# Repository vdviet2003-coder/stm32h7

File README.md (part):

# STM32H7 Sensorless FOC Motor Control

Firmware điều khiển động cơ PMSM theo phương pháp **Field-Oriented Control (FOC) không cảm biến vị trí (sensorless)** chạy trên vi điều khiển **STM32H723ZGTx**, sử dụng Sliding Mode Observer (SMO) để ước lượng góc và tốc độ rotor.

---

## Mục lục

1. [Tổng quan hệ thống](#1-tổng-quan-hệ-thống)
2. [Phần cứng và thông số động cơ](#2-phần-cứng-và-thông-số-động-cơ)
3. [Cấu trúc thư mục](#3-cấu-trúc-thư-mục)
4. [Sơ đồ khối điều khiển](#4-sơ-đồ-khối-điều-khiển)
5. [Luồng thực thi chính](#5-luồng-thực-thi-chính)
6. [Các module và logic chi tiết](#6-các-module-và-logic-chi-tiết)
   - 6.1 [conf.h – Cấu hình toàn cục](#61-confh--cấu-hình-toàn-cục)
   - 6.2 [FOC Transform – Clarke & Park](#62-foc-transform--clarke--park)
   - 6.3 [SVPWM – Space Vector PWM](#63-svpwm--space-vector-pwm)
   - 6.4 [ADC Driver – Đo dòng điện](#64-adc-driver--đo-dòng-điện)
   - 6.5 [Sensor – Hall & Encoder](#65-sensor--hall--encoder)
   - 6.6 [SMO – Sliding Mode Observer](#66-smo--sliding-mode-observer)
   - 6.7 [PID Controller](#67-pid-controller)
   - 6.8 [PI Clamping Controller](#68-pi-clamping-controller)
   - 6.9 [Speed Ramp Profiles](#69-speed-ramp-profiles)
   - 6.10 [UART DMA Library](#610-uart-dma-library)
7. [Máy trạng thái điều khiển (state machine)](#7-máy-trạng-thái-điều-khiển-state-machine)
   - 7.1 [Trạng thái chính (state)](#71-trạng-thái-chính-state)
   - 7.2 [Trạng thái SMO sensorless (state_smo)](#72-trạng-thái-smo-sensorless-state_smo)
8. [Cấu hình Timer và Ngắt](#8-cấu-hình-timer-và-ngắt)
9. [Thông số bộ điều khiển PID](#9-thông-số-bộ-điều-khiển-pid)
10. [Cấu hình Clock hệ thống](#10-cấu-hình-clock-hệ-thống)
11. [Build và nạp firmware](#11-build-và-nạp-firmware)

---

## 1. Tổng quan hệ thống

Hệ thống thực hiện điều khiển FOC hoàn chỉnh gồm 3 vòng điều khiển lồng nhau:

```
Tốc độ đặt (RPM/rad·s⁻¹)
        │
        ▼
  [Vòng tốc độ - PID]
        │  iq_ref
        ▼
  [Vòng dòng iq - PID] ──► vq
  [Vòng dòng id - PID] ──► vd    (id_ref = 0, kiểm soát từ thông)
        │
        ▼
  [Inv. Park] ──► vα, vβ
        │
        ▼
    [SVPWM] ──► TIM1 (PWM 3 pha)
        │
        ▼
     Động cơ
        │
        ▼
  [ADC] ─── iu, iv, iw
  [SMO] ─── θe, ωe  (sensorless)
        │
  [Clarke + Park] ──► id, iq (phản hồi)
```

---

## 2. Phần cứng và thông số động cơ

| Tham số | Giá trị |
|---------|---------|
| Vi điều khiển | STM32H723ZGTx |
| Toolchain | Keil MDK-ARM |
| Điện áp DC bus (VDC) | 60 V |
| Số cặp cực | 4 |
| Điện trở stator (Rs) | 5.83 Ω |
| Điện cảm stator (Ls) | 12.23 mH |
| Từ thông nam châm vĩnh cửu (ψf) | 0.0756 Wb |
| Tần số PWM | 20 kHz |
| Tần số vòng FOC | 40 kHz |
| Cảm biến dòng | LA-25-NP (Hall effect) |
| Điện trở đo | 120 Ω |
| Tỉ số biến đổi | 1:1000 (3 mA/A) |

### Phân công GPIO Hall sensor

| Tín hiệu | GPIO | Pin |
|----------|------|-----|
| Hall U | GPIOD | PIN_12 |
| Hall V | GPIOD | PIN_13 |
| Hall W | GPIOD | PIN_14 |

---

## 3. Cấu trúc thư mục

```
no encoder/
└── GPIO/
    ├── Core/
    │   ├── Inc/           # Header STM32 HAL (adc.h, tim.h, gpio.h, ...)
    │   └── Src/
    │       ├── main.c     # Vòng lặp chính, FOC ISR, khởi tạo
    │       ├── adc.c      # Cấu hình ADC HAL (injected mode)
    │       ├── tim.c      # Cấu hình Timer HAL
    │       ├── gpio.c     # Cấu hình GPIO
    │       ├── dma.c      # Cấu hình DMA
    │       └── usart.c    # Cấu hình UART
    ├── MDK-ARM/           # Mã nguồn ứng dụng + project Keil
    │   ├── conf.h         # *** Toàn bộ thông số hệ thống ***
    │   ├── foc_transform.c/h   # Clarke, Park, Inv.Park transforms
    │   ├── svpwm.c/h           # SVPWM 6 sector + bù dead-time
    │   ├── adc_driver.c/h      # Đọc dòng từ LA-25-NP
    │   ├── sensor.c/h          # Hall sensor + Encoder ABZ
    │   ├── smo.c/h             # Sliding Mode Observer
    │   ├── pid.c/h             # PID Tustin + anti-windup
    │   ├── pi_control.c/h      # PI clamping
    │   ├── scurve_ramp.c/h     # S-curve tốc độ
    │   ├── multi_ramp.c/h      # Multi-segment ramp
    │   └── uart_dma_lib.c/h    # UART DMA gửi/nhận
    └── Drivers/
        ├── CMSIS/         # CMSIS core, DSP library
        └── STM32H7xx_HAL_Driver/  # HAL drivers
```

---

## 4. Sơ đồ khối điều khiển

```
                    ┌─────────────────────────────────────────────┐
                    │               FOC LOOP (40 kHz - TIM6)      │
                    │                                             │
speed_ref ──►[Ramp]──►[PID_speed]──► iq_ref                     │
                                        │                        │
              id_ref=0 ───────────────► [PID_id] ──► vd          │
                    iq_ref ──────────► [PID_iq] ──► vq           │
                                                     │           │
                                              [Inv.Park(θe)]     │
                                                     │           │
                                              [SVPWM] ──► TIM1   │
                                                                 │
    ADC ──► [Clarke] ──► iα,iβ ──► [Park(θe)] ──► id, iq        │
                  │                                              │
                  └──► [SMO] ──► θe, ωe (sensorless feedback)   │
                    └─────────────────────────────────────────────┘
```

---

## 5. Luồng thực thi chính

### `main()` – Khởi tạo một lần

```
1. MPU_Config()           – Cấu hình vùng bộ nhớ (DMA non-cacheable)
2. SystemClock_Config()   – PLL: HSE → 440 MHz SYSCLK
3. MX_*_Init()            – Khởi tạo tất cả ngoại vi HAL
4. SVPWM_Init()           – Cài đặt TIM1 center-aligned PWM
5. SVPWM_Start()          – Bật PWM 3 pha + complementary
6. ADC_Driver_Init()      – Khởi động ADC injected mode
7. ADC_Driver_CalibrateOffset() – Lấy 100,000 mẫu để tính offset
8. Hall_Sensor_Init()     – Đọc trạng thái Hall ban đầu
9. Encoder_Sensor_Init()  – Cấu hình TIM2 (encoder mode)
10. UART_DMA_Init()       – Bật UART1 DMA RX/TX
11. PID_Init(x3)          – Khởi tạo 3 vòng PID (Id, Iq, Speed)
12. SMO_Init()            – Khởi tạo Sliding Mode Observer
13. while(1) {}           – Vòng lặp trống (mọi xử lý qua ISR)
```

---

## 6. Các module và logic chi tiết

### 6.1 `conf.h` – Cấu hình toàn cục

File duy nhất chứa tất cả hằng số hệ thống. Thay đổi thông số ở đây sẽ tác động toàn bộ firmware.

```c
#define POLE_PAIRS          4.0f
#define MOTOR_PWM_FREQ      20000.0f   // Hz
#define MOTOR_SPEED_CALC_FREQ 40000.0f // Hz (vòng FOC)
#define MOTOR_RS            5.83f      // Ω
#define MOTOR_LS            0.01223f   // H
#define MOTOR_PSI_F         0.075595f  // Wb
#define VDC_BUS             60.0f      // V
```

---

### 6.2 FOC Transform – Clarke & Park

**File**: `foc_transform.c/h`

Thực hiện các phép biến đổi tọa độ cơ bản của FOC:

#### Clarke Transform (3 pha → αβ cố định)
$$i_\alpha = \frac{2}{3}i_u - \frac{1}{3}i_v - \frac{1}{3}i_w$$
$$i_\beta = \frac{1}{\sqrt{3}}(i_v - i_w)$$

#### Park Transform (αβ → dq quay theo rotor)
$$i_d = i_\alpha \cos\theta_e + i_\beta \sin\theta_e$$
$$i_q = -i_\alpha \sin\theta_e + i_\beta \cos\theta_e$$

#### Inverse Park (dq → αβ)
$$v_\alpha = v_d \cos\theta_e - v_q \sin\theta_e$$
$$v_\beta = v_d \sin\theta_e + v_q \cos\theta_e$$

> **Lưu ý**: Dùng biến đổi **amplitude-invariant** (không nhân 2/3), phù hợp với điều khiển dòng trực tiếp.

---

### 6.3 SVPWM – Space Vector PWM

**File**: `svpwm.c/h`

Thuật toán SVPWM 6 sector, center-aligned, với bù dead-time tự động.

#### Các bước tính toán:

1. **Xác định sector** – Dùng phương pháp dấu (Sign Method):
   ```
   U1 = Vβ
   U2 = (√3/2)·Vα - 0.5·Vβ
   U3 = -(√3/2)·Vα - 0.5·Vβ
   N = sign(U1) + 2·sign(U2) + 4·sign(U3)  → tra bảng sector_table[]
   ```

2. **Tính thời gian vector X, Y, Z** (chuẩn hóa):
   $$X = \frac{\sqrt{3} V_\beta}{V_{DC}}, \quad Y = \frac{1.5V_\alpha + 0.5\sqrt{3}V_\beta}{V_{DC}}, \quad Z = \frac{1.5V_\alpha - 0.5\sqrt{3}V_\beta}{V_{DC}}$$

3. **Gán Tx, Ty theo sector** và xử lý overmodulation (chuẩn hóa nếu Tx+Ty > 1)

4. **Tính duty cycle 3 pha**:
   $$T_a = 0.5 + \frac{V_\alpha}{V_{DC}}, \quad T_b = 0.5 + \frac{-0.5V_\alpha + \frac{\sqrt{3}}{2}V_\beta}{V_{DC}}$$

5. **Bù dead-time** (tự động theo chiều dòng điện):
   - Dead-time: 0.484 µs (= 133 chu kỳ / 275 MHz)
   - Điện áp diode: 0.8 V
   - Bù dương/âm tùy thuộc vào dấu dòng pha

6. **Ghi CCR** vào TIM1 (Center-aligned mode)

---

### 6.4 ADC Driver – Đo dòng điện

**File**: `adc_driver.c/h`

Đọc dòng điện từ 3 cảm biến **LA-25-NP** (Hall effect, ratio 1:1000) qua ADC injected mode đồng bộ với PWM.

#### Công thức chuyển đổi:
$$I_P = \frac{2 \cdot V_{ADC} + V_{offset}}{-R_m \cdot n} = \frac{2 \cdot V_{ADC} - 2.5}{-120 \times 0.003}$$

Trong đó:
- $V_{ADC}$: điện áp đọc từ ADC (0..3.3V)
- $V_{offset}$ = -2.5 V (điểm zero của cảm biến)
- $R_m$ = 120 Ω (điện trở đo)
- $n$ = 0.003 (tỉ số biến đổi = 3mA/A)

#### Hiệu chỉnh offset:
Khi khởi động, `ADC_Driver_CalibrateOffset()` lấy **100,000 mẫu** ở trạng thái không tải để xác định giá trị offset DC, bù vào các lần đọc sau.

---

### 6.5 Sensor – Hall & Encoder

**File**: `sensor.c/h`

#### Hall Sensor
- 3 bit Hall (U, V, W) → 6 bước (step 1..6)
- Mỗi bước tương ứng góc điện 60°
- `HallSensor_Update()` gọi trong `HAL_TIM_IC_CaptureCallback` (TIM4)
- `Sensor_Get_Electrical_Angle_Hall()` trả về góc điện (rad)

| Step | Góc điện |
|------|----------|
| 1    | 0°       |
| 2    | 60°      |
| 3    | 120°     |
| 4    | 180°     |
| 5    | 240°     |
| 6    | 300°     |

#### Encoder ABZ
- TIM2 (32-bit) ở chế độ encoder quadrature
- 2500 PPR × 4 = 10,000 counts/vòng cơ
- `EncoderSensor_Update()` gọi trong TIM3 ISR (1 kHz)
- Hỗ trợ 3 phương pháp tính tốc độ:
  - **M method**: đếm xung trong thời gian cố định (tốc độ cao)
  - **T method**: đo thời gian giữa xung (tốc độ thấp)
  - **M/T method**: kết hợp hai phương pháp
  - **AUTO**: tự động chọn theo tốc độ

#### Bù trễ góc (Angle Prediction)
Trong vòng FOC, góc điện được dự đoán trước để bù trễ tính toán và ADC:
$$\theta_{pred} = \theta_{enc} + \omega_e \cdot (T_s + t_{delay})$$
Trong đó $t_{delay}$ = 3.87 µs (trễ ADC + tính toán).

---

### 6.6 SMO – Sliding Mode Observer

**File**: `smo.c/h`

Observer phi tuyến để ước lượng góc và tốc độ rotor **không cần encoder vật lý**. Triển khai theo mô hình dòng điện stator trong hệ tọa độ tĩnh αβ, kết hợp bộ lọc thông thấp và PLL để trích xuất sức phản điện (back-EMF).

---

#### Nguyên lý tổng quát

```
  [u_α, u_β]           [i_α, i_β]
       │                    │
       ▼                    │
  ┌─────────────────┐       │
  │  Mô hình dòng   │◄──────┘   (sai lệch → z_α, z_β)
  │  điện stator    │
  │  (Euler)        │──► [î_α, î_β]
  └────────┬────────┘
           │ z_α, z_β (sliding output)
           ▼
     [LPF 500 Hz]──► [ê_α, ê_β]  (back-EMF ước lượng)
           │
           ▼
       [PLL 200 Hz]──► θ_est, ω_est
           │
           ▼
   [Bù pha LPF]──► θ_compensated
```

---

#### Bước 1 – Hàm trượt (Sliding function) với deadzone

Để giảm chattering (dao động cao tần tại mặt trượt), hàm sign được thay bằng hàm tuyến tính trong vùng deadzone:

```c
static inline float sign_function(float x, float deadzone) {
    if      (x >  deadzone) return  1.0f;
    else if (x < -deadzone) return -1.0f;
    else                    return  x / deadzone;  // tuyến tính trong [-dz, +dz]
}
```

Ngõ ra khuếch đại trượt:

$$
z_{\alpha} = K_s \cdot \text{sign}(i_{\alpha,est} - i_{\alpha},\ 0.1\,\text{A})
$$

$$
z_{\beta} = K_s \cdot \text{sign}(i_{\beta,est} - i_{\beta},\ 0.1\,\text{A})
$$

Hệ số trượt $K_s$ chọn đủ lớn để đảm bảo điều kiện trượt:
$$K_s = 1.5 \cdot \omega_{max,elec} \cdot \psi_f \quad [\text{V}]$$

Ví dụ: $\omega_{max}$ = 3000 RPM × 4 pp × 2π/60 ≈ 1257 rad/s → $K_s = 1.5 \times 1257 \times 0.0756 \approx 142\,\text{V}$

---

#### Bước 2 – Mô hình dòng điện stator (tích phân Euler)

$$\hat{i}_{\alpha}[k+1] = \hat{i}_{\alpha}[k] + \frac{T_s}{L_s}\left(u_\alpha - R_s \hat{i}_{\alpha}[k] - z_\alpha\right)$$
$$\hat{i}_{\beta}[k+1]  = \hat{i}_{\beta}[k]  + \frac{T_s}{L_s}\left(u_\beta  - R_s \hat{i}_{\beta}[k]  - z_\beta\right)$$

Khi đạt chế độ trượt ($s_\alpha \to 0$, $s_\beta \to 0$), $z_\alpha \approx e_\alpha$ và $z_\beta \approx e_\beta$ (sức phản điện thực).

---

#### Bước 3 – Lọc thông thấp trích xuất back-EMF

Bộ lọc IIR bậc 1 (forward Euler) với $f_c$ = 500 Hz:

$$
\hat{e}_{\alpha}[k] = \alpha_f \cdot z_{\alpha} + (1-\alpha_f) \cdot \hat{e}_{\alpha}[k-1]
$$

$$
\hat{e}_{\beta}[k] = \alpha_f \cdot z_{\beta} + (1-\alpha_f) \cdot \hat{e}_{\beta}[k-1]
$$

Hệ số lọc:
$$\alpha_f = \frac{\omega_c T_s}{1 + \omega_c T_s}, \quad \omega_c = 2\pi \times 500 \approx 3141.6\,\text{rad/s}$$

Tại $T_s = 25\,\mu\text{s}$: $\alpha_f \approx 0.0728$

> **Lưu ý**: Bộ lọc thông thấp gây trễ pha phụ thuộc tốc độ, được bù lại ở bước 5.

---

#### Bước 4 – PLL ước lượng góc và tốc độ

Tín hiệu lỗi PLL (cross-product):

$$
\varepsilon = \hat{e}_{\beta} \cos\hat{\theta} - \hat{e}_{\alpha} \sin\hat{\theta}
$$

Khi hội tụ: $\hat{\theta} \to \theta_{real}$ → $\varepsilon \to 0$.

Bộ điều khiển PI của PLL:
$$\hat{\omega} = K_{p,PLL} \cdot \varepsilon + K_{i,PLL} \cdot \int \varepsilon \, dt$$

Tích phân góc (Euler):
$$\hat{\theta}[k+1] = \hat{\theta}[k] + \hat{\omega} \cdot T_s$$

Chuẩn hóa về $[0, 2\pi)$ sau mỗi bước.

**Anti-windup tốc độ**: khi $|\hat{\omega}| > \omega_{max}$, giới hạn cứng và reset tích phân:
```c
if (omega_pll > smo->omega_max) {
    omega_pll = smo->omega_max;
    smo->pll_integral = omega_pll / smo->Ki_pll;   // back-calculation
}
```

**Thông số PLL** (thiết kế theo $\zeta = 1/\sqrt{2}$, $f_n$ = 200 Hz):

| Tham số | Công thức | Giá trị |
|---------|-----------|---------|
| $\omega_n$ | $2\pi \times 200$ | 1256.6 rad/s |
| $K_{p,PLL}$ | $\sqrt{2} \cdot \omega_n$ | ≈ 1777 |
| $K_{i,PLL}$ | $\omega_n^2$ | ≈ 1.58 × 10⁶ |

---

#### Bước 5 – Bù pha bộ lọc thông thấp (`SMO_GetCompensatedTheta`)

Bộ lọc thông thấp 500 Hz gây trễ pha phụ thuộc tốc độ. Góc thực được bù động:
$$\phi_{delay} = \arctan\!\left(\frac{\hat{\omega}}{\omega_c}\right)$$
$$\theta_{comp} = \hat{\theta} + \phi_{delay}$$

```c
float SMO_GetCompensatedTheta(SMO_Handle *smo) {
    float wc = 2.0f * M_PI * smo->fc_filter;
    float phase_delay = atan2f(smo->omega_est, wc);
    return smo->theta_est + phase_delay;
}
```

> Khác với xấp xỉ cố định $+\pi/2$, cách này bù chính xác ở mọi tốc độ: khi $\hat{\omega} \ll \omega_c$ thì $\phi \to 0$; khi $\hat{\omega} \gg \omega_c$ thì $\phi \to \pi/2$.

---

#### Tóm tắt cấu trúc `SMO_Handle`

| Trường | Ý nghĩa | Đơn vị |
|--------|---------|--------|
| `Rs`, `Ls`, `psi_f` | Thông số điện động cơ | Ω, H, Wb |
| `pole_pairs` | Số cặp cực | – |
| `Ks` | Hệ số khuếch đại trượt | V |
| `fc_filter`, `alpha_filter` | Bộ lọc LPF 500 Hz | Hz, – |
| `Kp_pll`, `Ki_pll` | Gains PI của PLL | – |
| `ialpha_est`, `ibeta_est` | Dòng ước lượng | A |
| `ealpha_est`, `ebeta_est` | Back-EMF ước lượng | V |
| `theta_est` | Góc điện ước lượng | rad |
| `omega_est` | Tốc độ điện ước lượng | rad/s |
| `pll_integral` | Tích phân PLL | – |
| `omega_max`, `omega_min` | Giới hạn tốc độ điện | rad/s |

---

#### API

| Hàm | Mô tả |
|-----|-------|
| `SMO_Init(...)` | Khởi tạo, tự tính Ks, α_filter, Kp/Ki_pll |
| `SMO_Update(smo, uα, uβ, iα, iβ, dt)` | Gọi mỗi chu kỳ FOC (40 kHz) |
| `SMO_GetCompensatedTheta(smo)` | Trả về góc đã bù trễ LPF (rad) |
| `SMO_GetOmega(smo)` | Trả về tốc độ điện (rad/s) |
| `SMO_GetSpeedRPM(smo)` | Trả về tốc độ cơ (RPM) |

---

### 6.7 PID Controller

**File**: `pid.c/h`

Bộ điều khiển PID rời rạc dùng **Tustin (bilinear) discretization** để bảo toàn tính ổn định.

#### Rời rạc hóa Tustin:
$$u[k] = u[k-1] + \alpha \cdot e[k] + \beta \cdot e[k-1] + \gamma \cdot e[k-2]$$

Trong đó:
$$\alpha = K_p + \frac{K_i T}{2} + \frac{2K_d}{T}, \quad \beta = K_i T - \frac{4K_d}{T}, \quad \gamma = -K_p + \frac{K_i T}{2} + \frac{2K_d}{T}$$

#### Anti-windup:
Khi ngõ ra bão hòa (|u| = u_max), bộ tích phân tạm dừng (conditional integration).

---

### 6.8 PI Clamping Controller

**File**: `pi_control.c/h`

Bộ PI đơn giản với clamping (giới hạn cứng ngõ ra):
$$I_{prev} = I_{prev} + K_i \cdot T_s \cdot e$$
$$u = \text{clamp}(K_p \cdot e + I_{prev}, U_{min}, U_{max})$$

Dùng làm bộ điều khiển dự phòng thay thế cho PID trong trường hợp cần tuning nhanh.

---

### 6.9 Speed Ramp Profiles

#### S-Curve Ramp (`scurve_ramp.c/h`)
Tạo profile tốc độ dạng chữ S để tránh thay đổi đột ngột:
- Tham số: gia tốc tăng, gia tốc giảm, hằng số thời gian lọc τ
- Lọc exponential qua linear ramp → output mượt mà

#### Multi-Segment Ramp (`multi_ramp.c/h`)
Gia tốc khác nhau ở các vùng tốc độ khác nhau:
- Dưới ngưỡng (`threshold`): dùng `AccUp_1`, `AccDown_1` (gia tốc thấp vùng thấp tốc)
- Trên ngưỡng: dùng `AccUp_2`, `AccDown_2` (gia tốc cao vùng cao tốc)

Cấu hình mặc định: `threshold=5`, `up1=10`, `up2=10`, `down1=20`, `down2=20` (rad/s²)

---

### 6.10 UART DMA Library

**File**: `uart_dma_lib.c/h`

Giao tiếp UART1 bằng DMA không chặn (non-blocking):
- **TX**: Gửi chuỗi/dữ liệu qua DMA, không chờ
- **RX**: Nhận bằng DMA + IDLE interrupt để phát hiện kết thúc frame
- Hỗ trợ callback: `UART_DMA_RegisterRxCallback()` để xử lý dữ liệu nhận

---

## 7. Máy trạng thái điều khiển (State Machine)

### 7.1 Trạng thái chính (`state`)

Biến `state` điều khiển chế độ hoạt động của vòng FOC (TIM6 ISR, 40kHz):

```
┌─────────────────────────────────────────────────────────────────────┐
│  state = 0  │  DỪNG – PWM output = 0, reset SMO, tắt LED          │
├─────────────────────────────────────────────────────────────────────┤
│  state = 1  │  ALIGN – Căn chỉnh rotor:                           │
│             │  · InvPark(Id=0.8A, Iq=0, θ=0) → vα, vβ            │
│             │  · Reset encoder sau khi căn                         │
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
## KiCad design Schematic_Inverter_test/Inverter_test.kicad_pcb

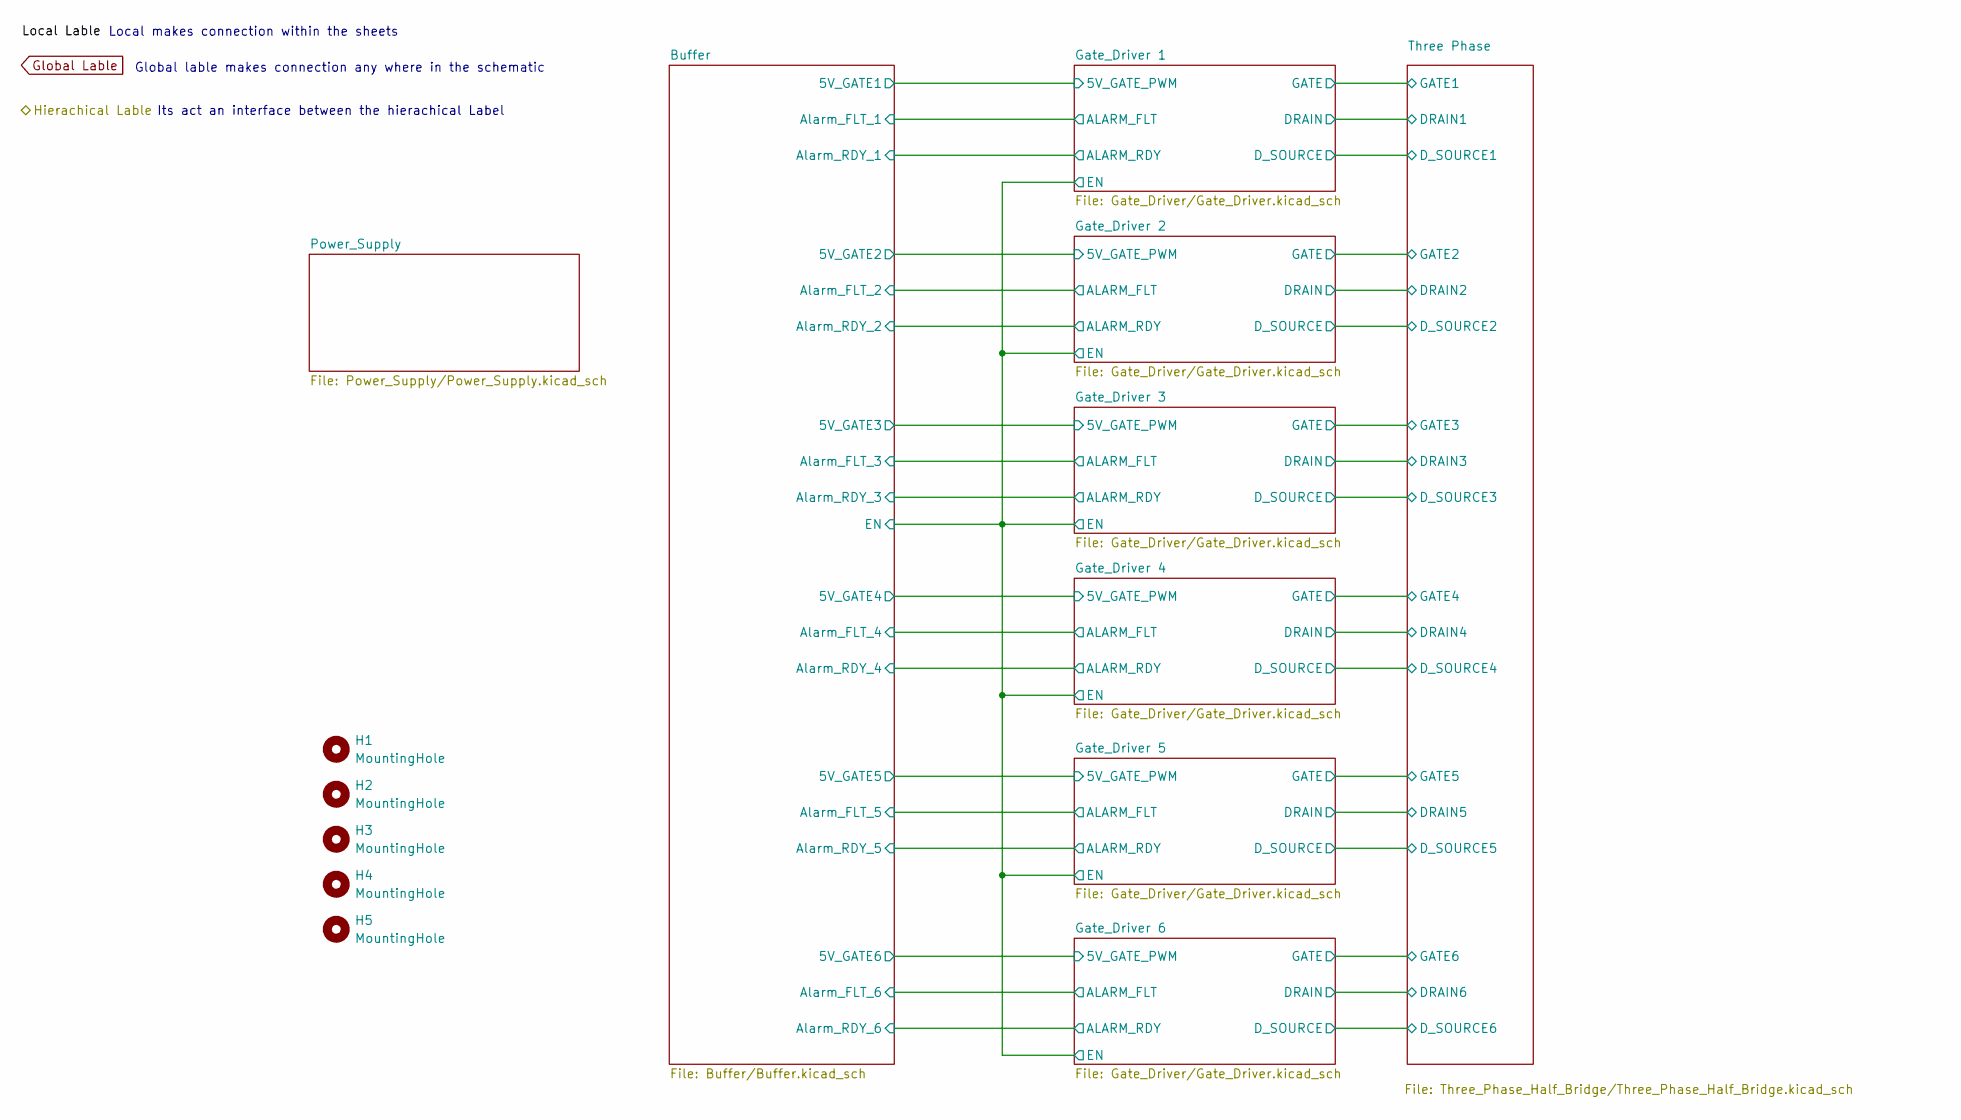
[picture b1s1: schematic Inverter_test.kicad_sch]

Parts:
H1, H2, H3, H4, H5: MountingHole; MountingHole_3.2mm_M3

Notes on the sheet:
Its act an interface between the hierachical Label
Global lable makes connection any where in the schematic
Local makes connection within the sheets

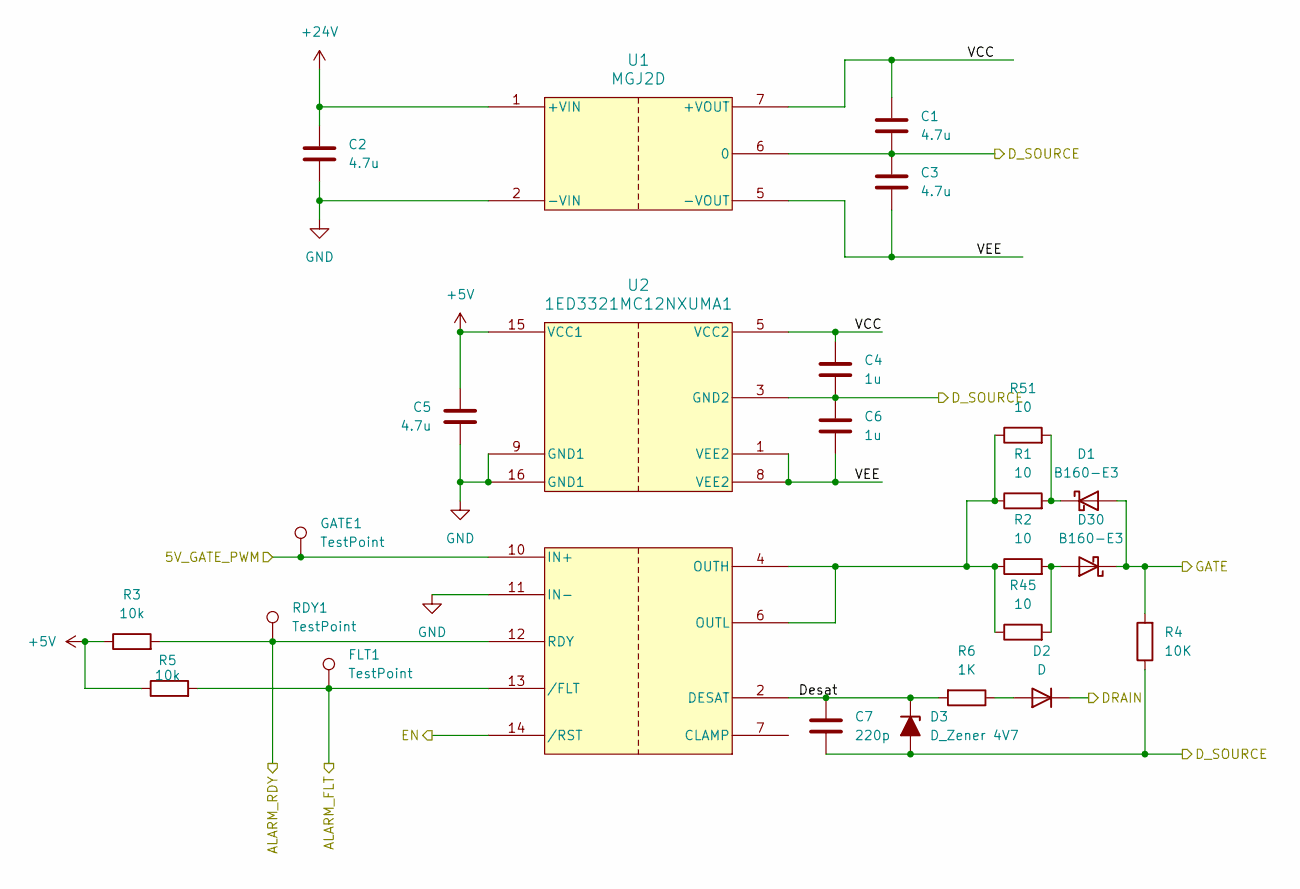
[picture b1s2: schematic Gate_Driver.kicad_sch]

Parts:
C1, C2, C3, C5: 4.7u; C_1206_3216Metric_Pad1.33x1.80mm_HandSolder
C4, C6: 1u; C_1206_3216Metric_Pad1.33x1.80mm_HandSolder
C7: 220p; C_1206_3216Metric_Pad1.33x1.80mm_HandSolder
D1, D30: B160-E3; D_SMA
D2: D; D_SMA
D3: D_Zener 4V7; D_SMA
FLT1: TestPoint; Pin_D0.7mm_L6.5mm_W1.8mm_FlatFork
GATE1: TestPoint; Pin_D0.7mm_L6.5mm_W1.8mm_FlatFork
R1, R2, R45, R51: 10; R_1206_3216Metric_Pad1.30x1.75mm_HandSolder
R3, R5: 10k; R_1206_3216Metric_Pad1.30x1.75mm_HandSolder
R4: 10K; R_1206_3216Metric_Pad1.30x1.75mm_HandSolder
R6: 1K; R_1206_3216Metric_Pad1.30x1.75mm_HandSolder
RDY1: TestPoint; Pin_D0.7mm_L6.5mm_W1.8mm_FlatFork
U1: MGJ2D; MGJ2_MUR
U2: 1ED3321MC12NXUMA1; PG-DSO-16-40_INF-M

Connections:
+5V: C5.1, R3.1, R5.1, U2.15 (VCC1); also elsewhere on the board
+24V: C2.1, U1.1 (+VIN); also elsewhere on the board
/Buffer/5V_DRIVER_EN: U2.14 (/RST); also elsewhere on the board
/Buffer/5V_GATE1: GATE1.1, U2.10 (IN+); also elsewhere on the board
/Buffer/Alarm_FLT_1: FLT1.1, R5.2, U2.13 (/FLT); also elsewhere on the board
/Buffer/Alarm_RDY_1: R3.2, RDY1.1, U2.12 (RDY); also elsewhere on the board
/Gate_Driver 1/D_SOURCE: C1.2, C3.2, C4.2, C6.1, C7.2, D3.2 (A), R4.1, U1.6 (0), U2.3 (GND2); also elsewhere on the board
/Gate_Driver 1/Desat: C7.1, D3.1 (K), R6.2, U2.2 (DESAT)
/Gate_Driver 1/GATE: D1.2 (A), D30.1 (K), R4.2; also elsewhere on the board
/Gate_Driver 1/VCC: C1.1, C4.1, U1.7 (+VOUT), U2.5 (VCC2)
/Gate_Driver 1/VEE: C3.1, C6.2, U1.5 (-VOUT), U2.1 (VEE2), U2.8 (VEE2)
/Three Phase/+270V: D2.1 (K); also elsewhere on the board
GND: C2.2, C5.2, U1.2 (-VIN), U2.9 (GND1), U2.11 (IN-), U2.16 (GND1); also elsewhere on the board
unnamed: D1.1 (K), R1.2, R51.2
unnamed: D2.2 (A), R6.1
unnamed: D30.2 (A), R2.2, R45.2
unnamed: R1.1, R2.1, R45.1, R51.1, U2.4 (OUTH), U2.6 (OUTL)

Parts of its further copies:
C8, C9, C10, C12, C15, C16, C17, C19, C22, C23, C24, C26, C29, C30, C31, C33, C36, C37, C38, C40: 4.7u; C_1206_3216Metric_Pad1.33x1.80mm_HandSolder
C11, C13, C18, C20, C25, C27, C32, C34, C39, C41: 1u; C_1206_3216Metric_Pad1.33x1.80mm_HandSolder
C14, C21, C28, C35, C42: 220p; C_1206_3216Metric_Pad1.33x1.80mm_HandSolder
D4, D7, D10, D13, D16, D31, D32, D33, D34, D35: B160-E3; D_SMA
D5, D8, D11, D14, D17: D; D_SMA
D6, D9, D12, D15, D18: D_Zener 4V7; D_SMA
FLT2, FLT3, FLT4, FLT5, FLT6: TestPoint; Pin_D0.7mm_L6.5mm_W1.8mm_FlatFork
GATE2, GATE3, GATE4, GATE5, GATE6: TestPoint; Pin_D0.7mm_L6.5mm_W1.8mm_FlatFork
R7, R8, R13, R14, R19, R20, R25, R26, R31, R32, R46, R47, R48, R49, R50, R52, R53, R54, R55, R56: 10; R_1206_3216Metric_Pad1.30x1.75mm_HandSolder
R9, R11, R15, R17, R21, R23, R27, R29, R33, R35: 10k; R_1206_3216Metric_Pad1.30x1.75mm_HandSolder
R10, R16, R22, R28, R34: 10K; R_1206_3216Metric_Pad1.30x1.75mm_HandSolder
R12, R18, R24, R30, R36: 1K; R_1206_3216Metric_Pad1.30x1.75mm_HandSolder
RDY2, RDY3, RDY4, RDY5, RDY6: TestPoint; Pin_D0.7mm_L6.5mm_W1.8mm_FlatFork
U3, U5, U7, U9, U11: MGJ2D; MGJ2_MUR
U4, U6, U8, U10, U12: 1ED3321MC12NXUMA1; PG-DSO-16-40_INF-M

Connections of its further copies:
+5V: C12.1, C19.1, C26.1, C33.1, C40.1, R9.1, R11.1, R15.1, R17.1, R21.1, R23.1, R27.1, R29.1, R33.1, R35.1, U4.15 (VCC1), U6.15 (VCC1), U8.15 (VCC1), U10.15 (VCC1), U12.15 (VCC1); also elsewhere on the board
+24V: C9.1, C16.1, C23.1, C30.1, C37.1, U3.1 (+VIN), U5.1 (+VIN), U7.1 (+VIN), U9.1 (+VIN), U11.1 (+VIN); also elsewhere on the board
/Buffer/5V_DRIVER_EN: U4.14 (/RST), U6.14 (/RST), U8.14 (/RST), U10.14 (/RST), U12.14 (/RST); also elsewhere on the board
/Buffer/5V_GATE2: GATE2.1, U4.10 (IN+); also elsewhere on the board
/Buffer/5V_GATE3: GATE3.1, U6.10 (IN+); also elsewhere on the board
/Buffer/5V_GATE4: GATE4.1, U8.10 (IN+); also elsewhere on the board
/Buffer/5V_GATE5: GATE5.1, U10.10 (IN+); also elsewhere on the board
/Buffer/5V_GATE6: GATE6.1, U12.10 (IN+); also elsewhere on the board
/Buffer/Alarm_FLT_2: FLT2.1, R11.2, U4.13 (/FLT); also elsewhere on the board
/Buffer/Alarm_FLT_3: FLT3.1, R17.2, U6.13 (/FLT); also elsewhere on the board
/Buffer/Alarm_FLT_4: FLT4.1, R23.2, U8.13 (/FLT); also elsewhere on the board
/Buffer/Alarm_FLT_5: FLT5.1, R29.2, U10.13 (/FLT); also elsewhere on the board
/Buffer/Alarm_FLT_6: FLT6.1, R35.2, U12.13 (/FLT); also elsewhere on the board
/Buffer/Alarm_RDY_2: R9.2, RDY2.1, U4.12 (RDY); also elsewhere on the board
/Buffer/Alarm_RDY_3: R15.2, RDY3.1, U6.12 (RDY); also elsewhere on the board
/Buffer/Alarm_RDY_4: R21.2, RDY4.1, U8.12 (RDY); also elsewhere on the board
/Buffer/Alarm_RDY_5: R27.2, RDY5.1, U10.12 (RDY); also elsewhere on the board
/Buffer/Alarm_RDY_6: R33.2, RDY6.1, U12.12 (RDY); also elsewhere on the board
/Gate_Driver 2/D_SOURCE: C8.2, C10.2, C11.2, C13.1, C14.2, D6.2 (A), R10.1, U3.6 (0), U4.3 (GND2); also elsewhere on the board
/Gate_Driver 2/Desat: C14.1, D6.1 (K), R12.2, U4.2 (DESAT)
/Gate_Driver 2/GATE: D4.2 (A), D31.1 (K), R10.2; also elsewhere on the board
/Gate_Driver 2/VCC: C8.1, C11.1, U3.7 (+VOUT), U4.5 (VCC2)
/Gate_Driver 2/VEE: C10.1, C13.2, U3.5 (-VOUT), U4.1 (VEE2), U4.8 (VEE2)
/Gate_Driver 3/D_SOURCE: C15.2, C17.2, C18.2, C20.1, C21.2, D9.2 (A), R16.1, U5.6 (0), U6.3 (GND2); also elsewhere on the board
/Gate_Driver 3/Desat: C21.1, D9.1 (K), R18.2, U6.2 (DESAT)
/Gate_Driver 3/GATE: D7.2 (A), D32.1 (K), R16.2; also elsewhere on the board
/Gate_Driver 3/VCC: C15.1, C18.1, U5.7 (+VOUT), U6.5 (VCC2)
/Gate_Driver 3/VEE: C17.1, C20.2, U5.5 (-VOUT), U6.1 (VEE2), U6.8 (VEE2)
/Gate_Driver 4/D_SOURCE: C22.2, C24.2, C25.2, C27.1, C28.2, D12.2 (A), R22.1, U7.6 (0), U8.3 (GND2); also elsewhere on the board
/Gate_Driver 4/Desat: C28.1, D12.1 (K), R24.2, U8.2 (DESAT)
/Gate_Driver 4/GATE: D10.2 (A), D33.1 (K), R22.2; also elsewhere on the board
/Gate_Driver 4/VCC: C22.1, C25.1, U7.7 (+VOUT), U8.5 (VCC2)
/Gate_Driver 4/VEE: C24.1, C27.2, U7.5 (-VOUT), U8.1 (VEE2), U8.8 (VEE2)
/Gate_Driver 5/D_SOURCE: C29.2, C31.2, C32.2, C34.1, C35.2, D15.2 (A), R28.1, U9.6 (0), U10.3 (GND2); also elsewhere on the board
/Gate_Driver 5/Desat: C35.1, D15.1 (K), R30.2, U10.2 (DESAT)
/Gate_Driver 5/GATE: D13.2 (A), D34.1 (K), R28.2; also elsewhere on the board
/Gate_Driver 5/VCC: C29.1, C32.1, U9.7 (+VOUT), U10.5 (VCC2)
/Gate_Driver 5/VEE: C31.1, C34.2, U9.5 (-VOUT), U10.1 (VEE2), U10.8 (VEE2)
/Gate_Driver 6/D_SOURCE: C36.2, C38.2, C39.2, C41.1, C42.2, D18.2 (A), R34.1, U11.6 (0), U12.3 (GND2); also elsewhere on the board
/Gate_Driver 6/Desat: C42.1, D18.1 (K), R36.2, U12.2 (DESAT)
/Gate_Driver 6/GATE: D16.2 (A), D35.1 (K), R34.2; also elsewhere on the board
/Gate_Driver 6/VCC: C36.1, C39.1, U11.7 (+VOUT), U12.5 (VCC2)
/Gate_Driver 6/VEE: C38.1, C41.2, U11.5 (-VOUT), U12.1 (VEE2), U12.8 (VEE2)
/Three Phase/+270V: D8.1 (K), D14.1 (K); also elsewhere on the board
/Three Phase/U: D5.1 (K); also elsewhere on the board
/Three Phase/V: D11.1 (K); also elsewhere on the board
/Three Phase/W: D17.1 (K); also elsewhere on the board
GND: C9.2, C12.2, C16.2, C19.2, C23.2, C26.2, C30.2, C33.2, C37.2, C40.2, U3.2 (-VIN), U4.9 (GND1), U4.11 (IN-), U4.16 (GND1), U5.2 (-VIN), U6.9 (GND1), U6.11 (IN-), U6.16 (GND1), U7.2 (-VIN), U8.9 (GND1), U8.11 (IN-), U8.16 (GND1), U9.2 (-VIN), U10.9 (GND1), U10.11 (IN-), U10.16 (GND1), U11.2 (-VIN), U12.9 (GND1), U12.11 (IN-), U12.16 (GND1); also elsewhere on the board
unnamed: D4.1 (K), R7.2, R52.2
unnamed: D5.2 (A), R12.1
unnamed: D7.1 (K), R13.2, R53.2
unnamed: D8.2 (A), R18.1
unnamed: D10.1 (K), R19.2, R54.2
unnamed: D11.2 (A), R24.1
unnamed: D13.1 (K), R25.2, R55.2
unnamed: D14.2 (A), R30.1
unnamed: D16.1 (K), R31.2, R56.2
unnamed: D17.2 (A), R36.1
unnamed: D31.2 (A), R8.2, R46.2
unnamed: D32.2 (A), R14.2, R47.2
unnamed: D33.2 (A), R20.2, R48.2
unnamed: D34.2 (A), R26.2, R49.2
unnamed: D35.2 (A), R32.2, R50.2
unnamed: R7.1, R8.1, R46.1, R52.1, U4.4 (OUTH), U4.6 (OUTL)
unnamed: R13.1, R14.1, R47.1, R53.1, U6.4 (OUTH), U6.6 (OUTL)
unnamed: R19.1, R20.1, R48.1, R54.1, U8.4 (OUTH), U8.6 (OUTL)
unnamed: R25.1, R26.1, R49.1, R55.1, U10.4 (OUTH), U10.6 (OUTL)
unnamed: R31.1, R32.1, R50.1, R56.1, U12.4 (OUTH), U12.6 (OUTL)

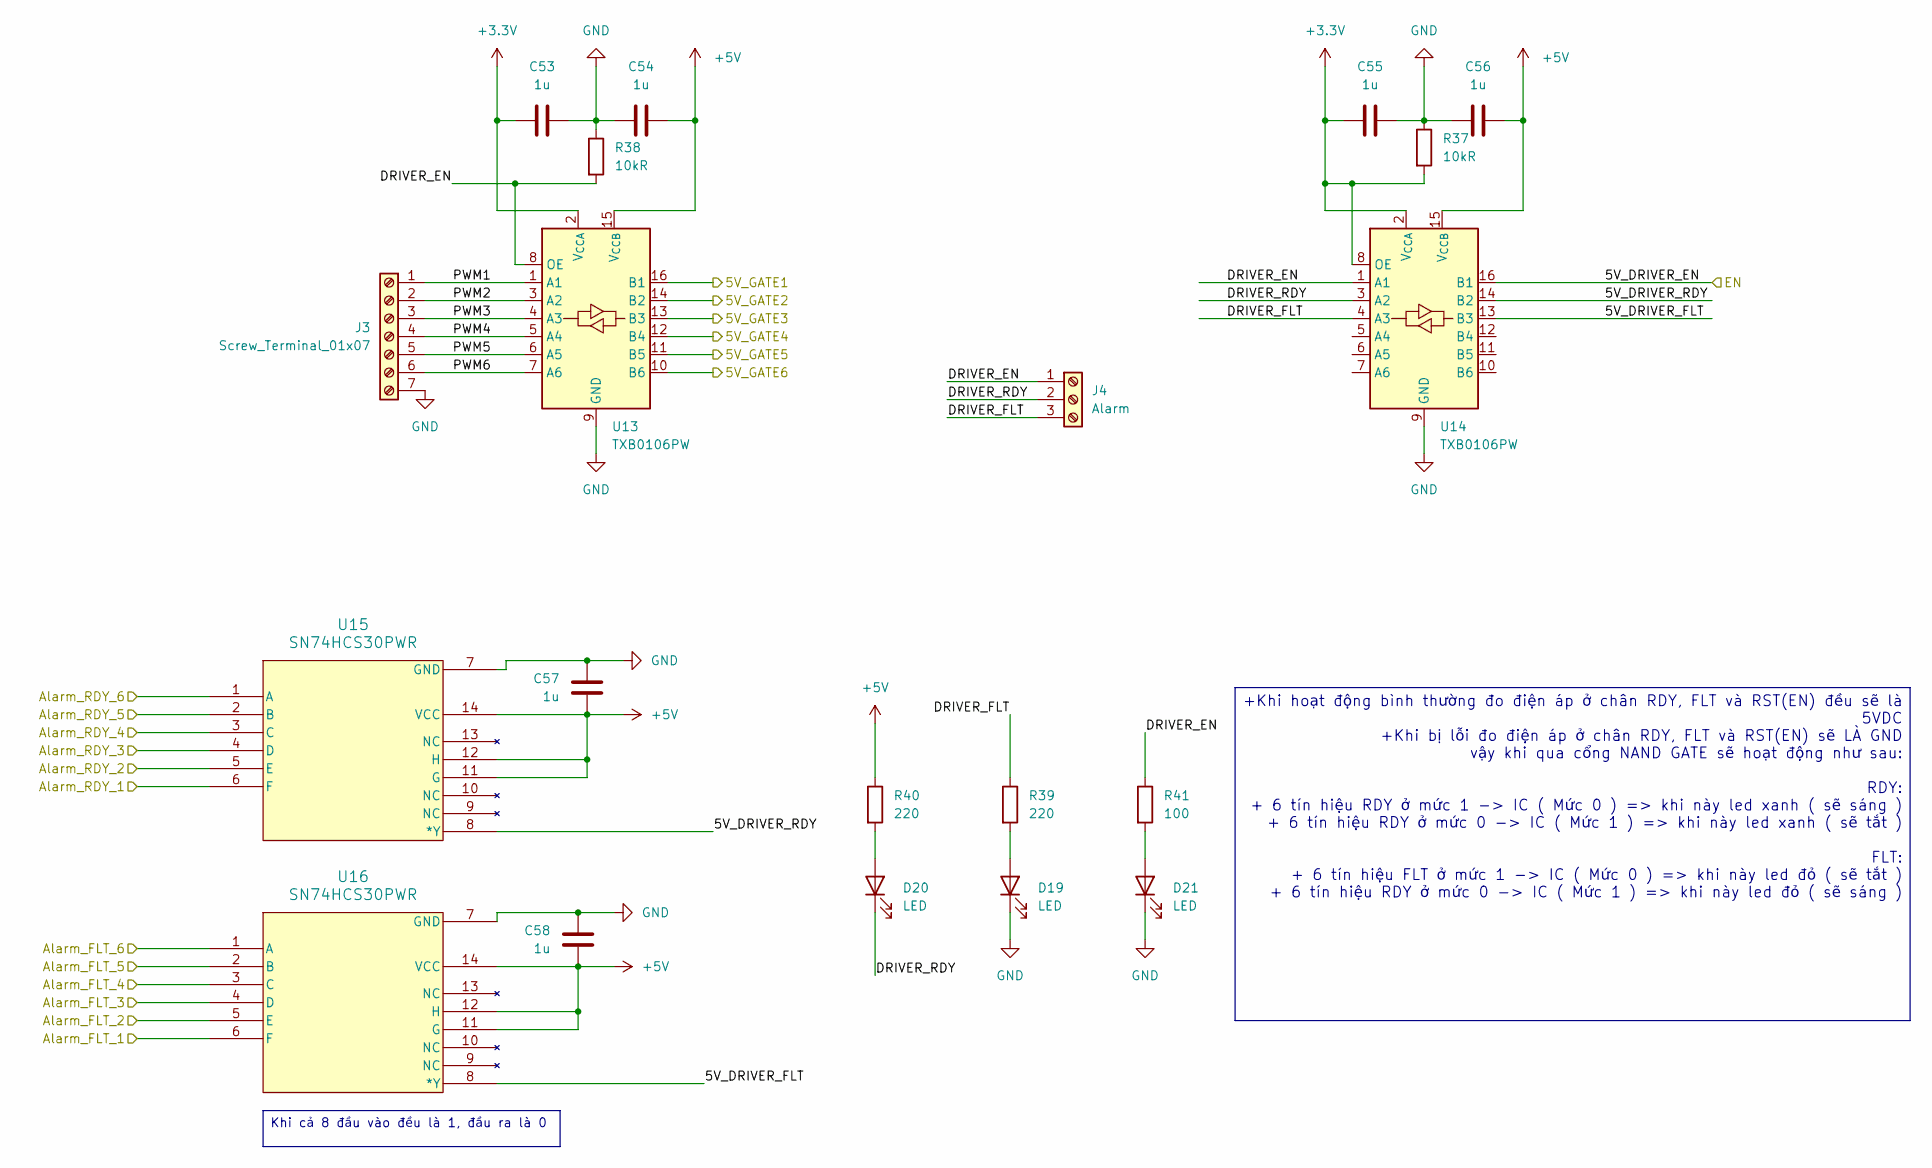
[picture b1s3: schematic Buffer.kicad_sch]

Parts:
C53, C54, C55, C56, C57, C58: 1u; C_1206_3216Metric_Pad1.33x1.80mm_HandSolder
D19, D20, D21: LED; LED_D3.0mm
J3: Screw_Terminal_01x07; TerminalBlock_Phoenix_MKDS-1,5-7_1x07_P5.00mm_Horizontal
J4: Alarm; TerminalBlock_Phoenix_MKDS-1,5-3_1x03_P5.00mm_Horizontal
R37, R38: 10kR; R_1206_3216Metric_Pad1.30x1.75mm_HandSolder
R39, R40: 220; R_1206_3216Metric_Pad1.30x1.75mm_HandSolder
R41: 100; R_1206_3216Metric_Pad1.30x1.75mm_HandSolder
U13, U14: TXB0106PW; TSSOP-16_4.4x5mm_P0.65mm
U15, U16: SN74HCS30PWR; SOIC-14_SN74HCS30PWR-M

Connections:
+3.3V: C53.2, C55.2, R37.2, U13.2 (V_{CCA}), U14.2 (V_{CCA}), U14.8 (OE); also elsewhere on the board
+5V: C54.1, C56.1, C57.2, C58.2, R40.1, U13.15 (V_{CCB}), U14.15 (V_{CCB}), U15.11 (G), U15.12 (H), U15.14 (VCC), U16.11 (G), U16.12 (H), U16.14 (VCC); also elsewhere on the board
/Buffer/5V_DRIVER_EN: U14.16 (B1); also elsewhere on the board
/Buffer/5V_DRIVER_FLT: U14.13 (B3), U16.8 (*Y)
/Buffer/5V_DRIVER_RDY: U14.14 (B2), U15.8 (*Y)
/Buffer/5V_GATE1: U13.16 (B1); also elsewhere on the board
/Buffer/5V_GATE2: U13.14 (B2); also elsewhere on the board
/Buffer/5V_GATE3: U13.13 (B3); also elsewhere on the board
/Buffer/5V_GATE4: U13.12 (B4); also elsewhere on the board
/Buffer/5V_GATE5: U13.11 (B5); also elsewhere on the board
/Buffer/5V_GATE6: U13.10 (B6); also elsewhere on the board
/Buffer/Alarm_FLT_1: U16.6 (F); also elsewhere on the board
/Buffer/Alarm_FLT_2: U16.5 (E); also elsewhere on the board
/Buffer/Alarm_FLT_3: U16.4 (D); also elsewhere on the board
/Buffer/Alarm_FLT_4: U16.3 (C); also elsewhere on the board
/Buffer/Alarm_FLT_5: U16.2 (B); also elsewhere on the board
/Buffer/Alarm_FLT_6: U16.1 (A); also elsewhere on the board
/Buffer/Alarm_RDY_1: U15.6 (F); also elsewhere on the board
/Buffer/Alarm_RDY_2: U15.5 (E); also elsewhere on the board
/Buffer/Alarm_RDY_3: U15.4 (D); also elsewhere on the board
/Buffer/Alarm_RDY_4: U15.3 (C); also elsewhere on the board
/Buffer/Alarm_RDY_5: U15.2 (B); also elsewhere on the board
/Buffer/Alarm_RDY_6: U15.1 (A); also elsewhere on the board
/Buffer/DRIVER_EN: J4.1, R38.2, R41.1, U13.8 (OE), U14.1 (A1)
/Buffer/DRIVER_FLT: J4.3, R39.1, U14.4 (A3)
/Buffer/DRIVER_RDY: D20.1 (K), J4.2, U14.3 (A2)
/Buffer/PWM1: J3.1, U13.1 (A1)
/Buffer/PWM2: J3.2, U13.3 (A2)
/Buffer/PWM3: J3.3, U13.4 (A3)
/Buffer/PWM4: J3.4, U13.5 (A4)
/Buffer/PWM5: J3.5, U13.6 (A5)
/Buffer/PWM6: J3.6, U13.7 (A6)
GND: C53.1, C54.2, C55.1, C56.2, C57.1, C58.1, D19.1 (K), D21.1 (K), J3.7, R37.1, R38.1, U13.9 (GND), U14.9 (GND), U15.7 (GND), U16.7 (GND); also elsewhere on the board
unnamed: D19.2 (A), R39.2
unnamed: D20.2 (A), R40.2
unnamed: D21.2 (A), R41.2

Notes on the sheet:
+Khi hoạt động bình thường đo điện áp ở chân RDY, FLT và RST(EN) đều sẽ là 5VDC +Khi bị lỗi đo điện áp ở chân RDY, FLT và RST(EN) sẽ LÀ GND vậy khi qua cổng NAND GATE sẽ hoạt động như sau: RDY: + 6 tín hiệu RDY ở mức 1 -> IC ( Mức 0 ) => khi này led xanh ( sẽ sáng ) + 6 tín hiệu RDY ở mức 0 -> IC (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
Khi cả 8 đầu vào đều là 1, đầu ra là 0

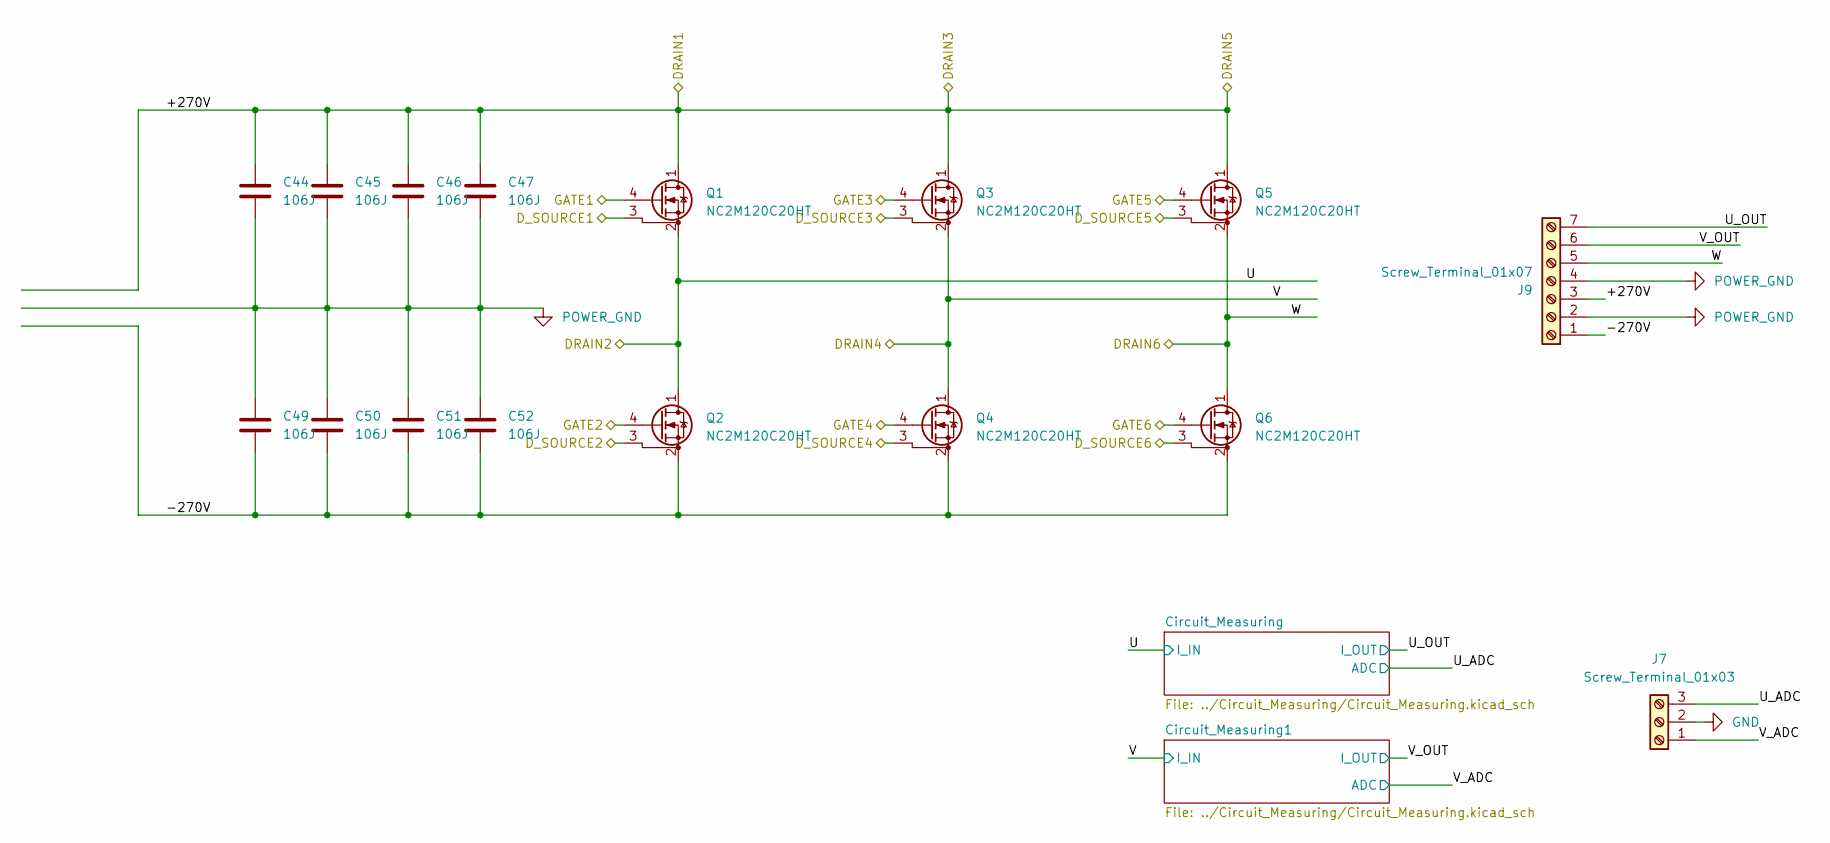
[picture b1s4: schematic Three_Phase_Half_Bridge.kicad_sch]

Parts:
C44, C45, C46, C47, C49, C50, C51, C52: 106J; C_Rect_L31.5mm_W15.0mm_P27.50mm_MKS4
J7: Screw_Terminal_01x03; TerminalBlock_Phoenix_MKDS-1,5-3_1x03_P5.00mm_Horizontal
J9: Screw_Terminal_01x07; Untitled
Q1, Q2, Q3, Q4, Q5, Q6: NC2M120C20HT; TO-247-4_Horizontal_TabUp

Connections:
/Gate_Driver 1/D_SOURCE: Q1.3 (DS); also elsewhere on the board
/Gate_Driver 1/GATE: Q1.4 (G); also elsewhere on the board
/Gate_Driver 2/D_SOURCE: Q2.3 (DS); also elsewhere on the board
/Gate_Driver 2/GATE: Q2.4 (G); also elsewhere on the board
/Gate_Driver 3/D_SOURCE: Q3.3 (DS); also elsewhere on the board
/Gate_Driver 3/GATE: Q3.4 (G); also elsewhere on the board
/Gate_Driver 4/D_SOURCE: Q4.3 (DS); also elsewhere on the board
/Gate_Driver 4/GATE: Q4.4 (G); also elsewhere on the board
/Gate_Driver 5/D_SOURCE: Q5.3 (DS); also elsewhere on the board
/Gate_Driver 5/GATE: Q5.4 (G); also elsewhere on the board
/Gate_Driver 6/D_SOURCE: Q6.3 (DS); also elsewhere on the board
/Gate_Driver 6/GATE: Q6.4 (G); also elsewhere on the board
/Three Phase/+270V: C44.1, C45.1, C46.1, C47.1, J9.3, Q1.1 (D), Q3.1 (D), Q5.1 (D); also elsewhere on the board
/Three Phase/-270V: C49.2, C50.2, C51.2, C52.2, J9.1, Q2.2 (S), Q4.2 (S), Q6.2 (S)
/Three Phase/U: Q1.2 (S), Q2.1 (D); also elsewhere on the board
/Three Phase/U_ADC: J7.3; also elsewhere on the board
/Three Phase/U_OUT: J9.7; also elsewhere on the board
/Three Phase/V: Q3.2 (S), Q4.1 (D); also elsewhere on the board
/Three Phase/V_ADC: J7.1; also elsewhere on the board
/Three Phase/V_OUT: J9.6; also elsewhere on the board
/Three Phase/W: J9.5, Q5.2 (S), Q6.1 (D); also elsewhere on the board
GND: J7.2; also elsewhere on the board
POWER_GND: C44.2, C45.2, C46.2, C47.2, C49.1, C50.1, C51.1, C52.1, J9.2, J9.4

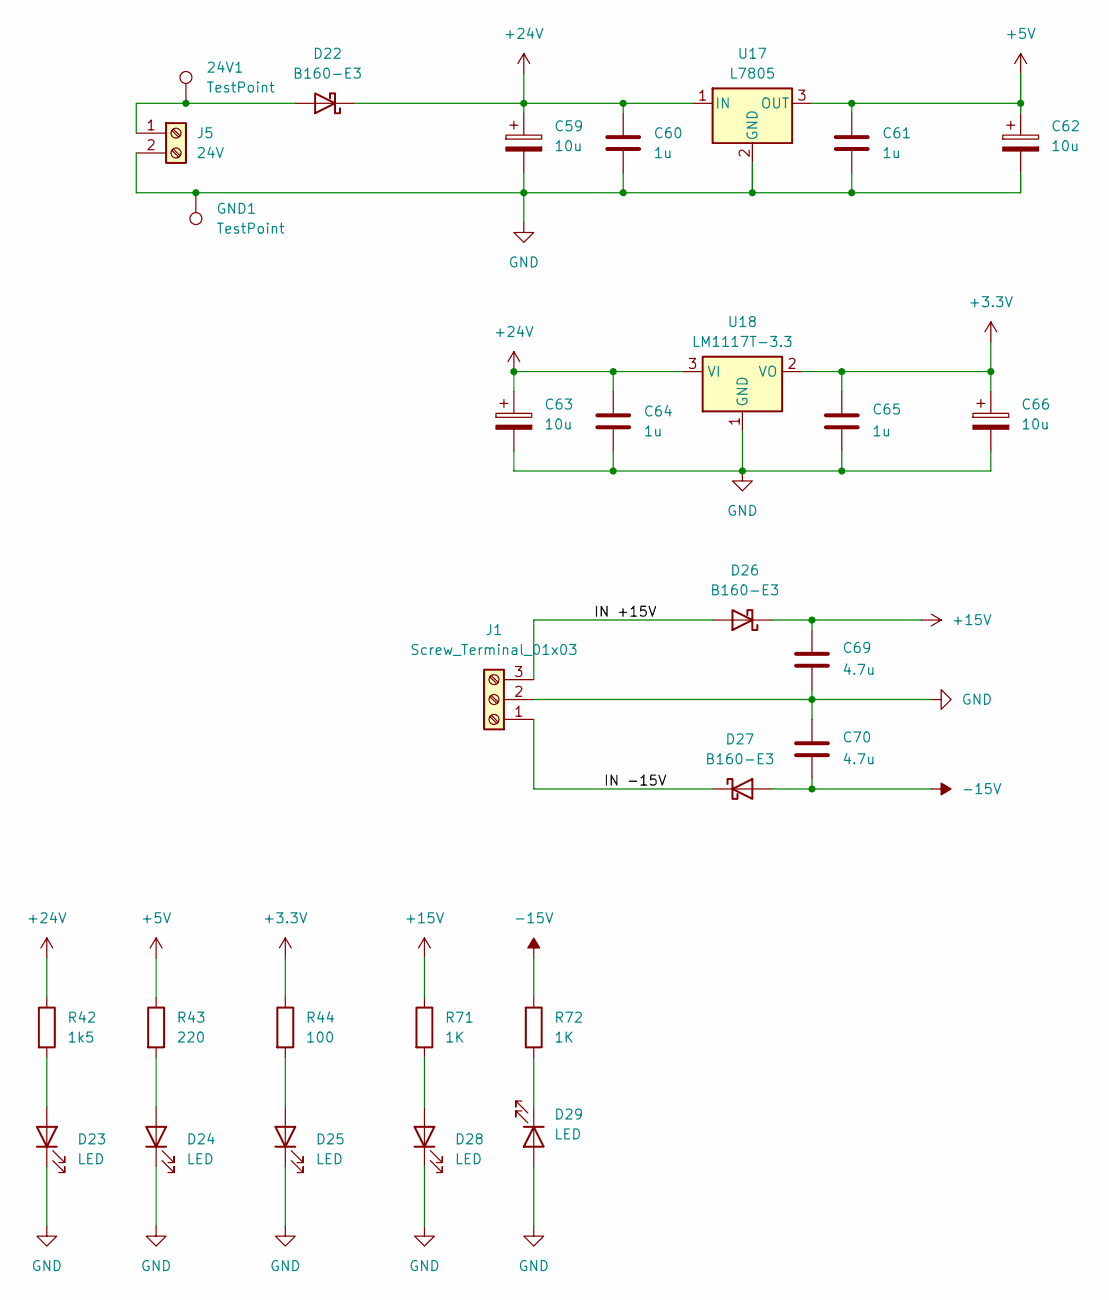
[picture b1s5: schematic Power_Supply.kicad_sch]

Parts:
24V1: TestPoint; Pin_D0.7mm_L6.5mm_W1.8mm_FlatFork
C59, C62, C63, C66: 10u; CP_Radial_D6.3mm_P2.50mm
C60, C61, C64, C65: 1u; C_Disc_D5.0mm_W2.5mm_P5.00mm
C69, C70: 4.7u; C_1206_3216Metric_Pad1.33x1.80mm_HandSolder
D22, D26, D27: B160-E3; D_SMA
D23, D24, D25, D28, D29: LED; LED_D3.0mm
GND1: TestPoint; Pin_D0.7mm_L6.5mm_W1.8mm_FlatFork
J1: Screw_Terminal_01x03; TerminalBlock_Phoenix_MKDS-1,5-3_1x03_P5.00mm_Horizontal
J5: 24V; TerminalBlock_Phoenix_MKDS-1,5-2_1x02_P5.00mm_Horizontal
R42: 1k5; R_1206_3216Metric_Pad1.30x1.75mm_HandSolder
R43: 220; R_1206_3216Metric_Pad1.30x1.75mm_HandSolder
R44: 100; R_1206_3216Metric_Pad1.30x1.75mm_HandSolder
R71, R72: 1K; R_1206_3216Metric_Pad1.30x1.75mm_HandSolder
U17: L7805; TO-220-3_Vertical
U18: LM1117T-3.3; TO-220-3_Vertical

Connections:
+3.3V: C65.1, C66.1, R44.1, U18.2 (VO); also elsewhere on the board
+5V: C61.1, C62.1, R43.1, U17.3 (OUT); also elsewhere on the board
+15V: C69.1, D26.1 (K), R71.1; also elsewhere on the board
+24V: C59.1, C60.1, C63.1, C64.1, D22.1 (K), R42.1, U17.1 (IN), U18.3 (VI); also elsewhere on the board
-15V: C70.2, D27.2 (A), R72.1; also elsewhere on the board
/Power_Supply/IN +15V: D26.2 (A), J1.3
/Power_Supply/IN -15V: D27.1 (K), J1.1
GND: C59.2, C60.2, C61.2, C62.2, C63.2, C64.2, C65.2, C66.2, C69.2, C70.1, D23.1 (K), D24.1 (K), D25.1 (K), D28.1 (K), D29.2 (A), GND1.1, J1.2, J5.2, U17.2 (GND), U18.1 (GND); also elsewhere on the board
unnamed: 24V1.1, D22.2 (A), J5.1
unnamed: D23.2 (A), R42.2
unnamed: D24.2 (A), R43.2
unnamed: D25.2 (A), R44.2
unnamed: D28.2 (A), R71.2
unnamed: D29.1 (K), R72.2
